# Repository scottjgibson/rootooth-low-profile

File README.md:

rootooth-low-profile
====================

My implementation of a bluetooth roomba interface.  It's very low profile and low cost

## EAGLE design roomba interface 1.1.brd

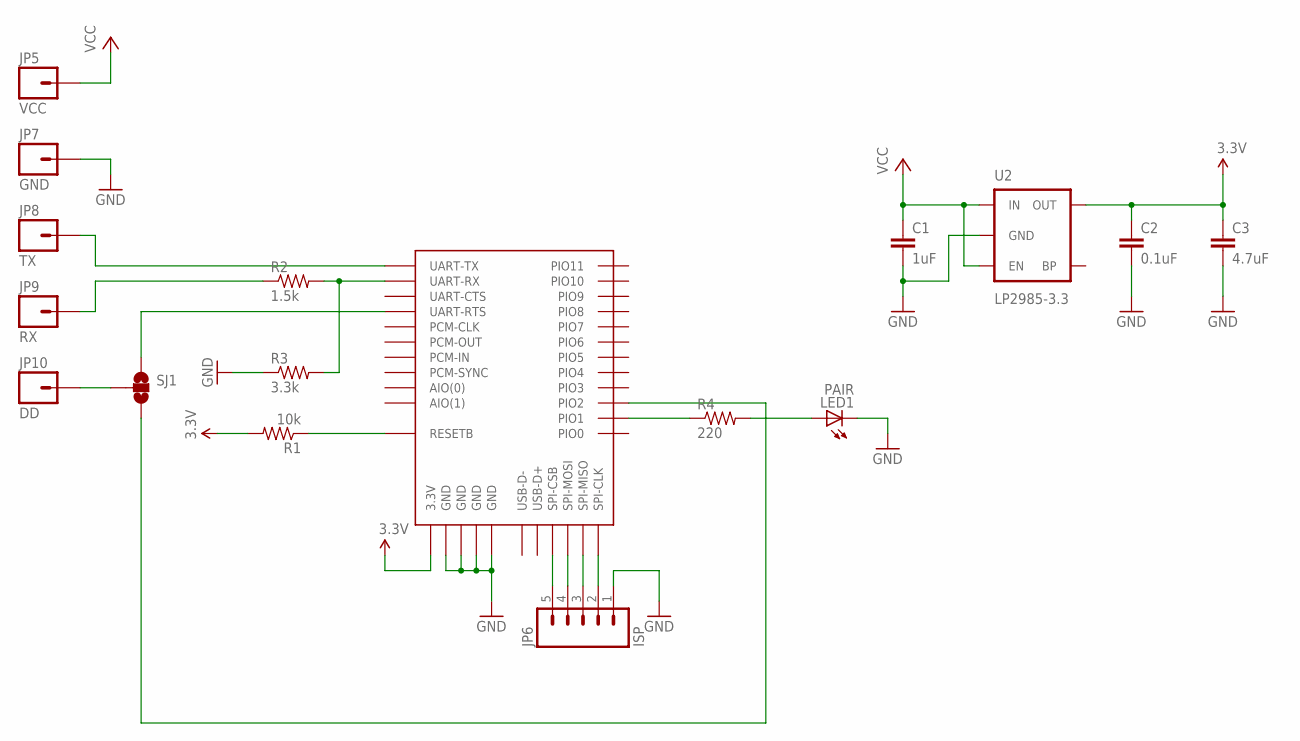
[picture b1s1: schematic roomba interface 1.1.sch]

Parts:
C1: 1uF; 0805
C2: 0.1uF; 0805
C3: 4.7uF; 0805
JP5: VCC; 1X01
JP6: ISP; 1X05
JP7: GND; 1X01
JP8: TX; 1X01
JP9: RX; 1X01
JP10: DD; 1X01
LED1: PAIR; LED-0603
R1: 10k; 0805
R2: 1.5k; 0805
R3: 3.3k; 0805
R4: 220; 0805
SJ1: SOLDERJUMPER_2WAYT; SJ_2
U2: LP2985-3.3; SOT23-5
U$1: BTM400_6B

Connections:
3.3V: C2.1, C3.1, R1.2, U2.5 (OUT), U$1.3.3V
GND: C1.2, C2.2, C3.2, JP6.1, JP7.1, LED1.C, R3.1, U2.2 (GND), U$1.GND@1 (GND), U$1.GND@2 (GND), U$1.GND@3 (GND), U$1.GND@4 (GND)
unnamed: R1.1, U$1.RESETB
unnamed: JP9.1, R2.1
unnamed: R2.2, R3.2, U$1.UART-RX
unnamed: JP8.1, U$1.UART-TX
unnamed: JP6.5, U$1.SPI-CSB
unnamed: JP6.4, U$1.SPI-MOSI
unnamed: JP6.3, U$1.SPI-MISO
unnamed: JP6.2, U$1.SPI-CLK
unnamed: SJ1.1, U$1.UART-RTS
unnamed: R4.1, U$1.PIO(1) (PIO1)
unnamed: LED1.A, R4.2
unnamed: JP10.1, SJ1.2
unnamed: SJ1.3, U$1.PIO(2) (PIO2)
VCC: C1.1, JP5.1, U2.1 (IN), U2.3 (EN)

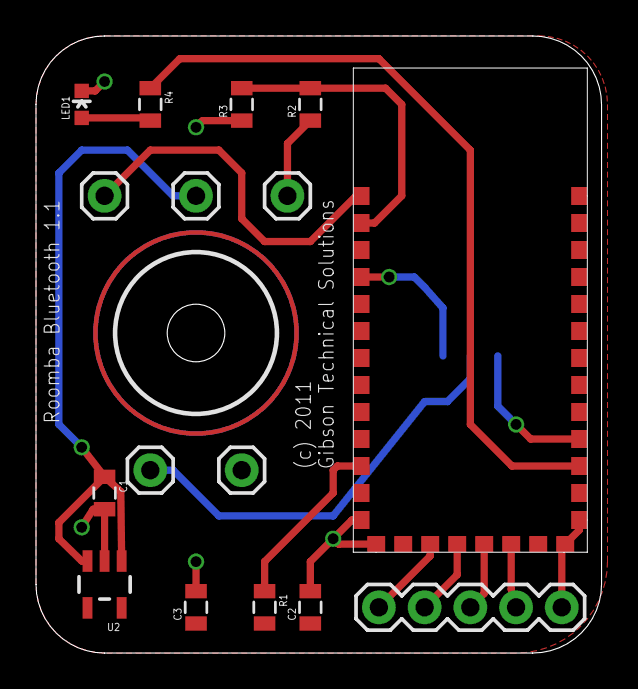
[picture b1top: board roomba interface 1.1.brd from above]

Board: 2 copper layers, 31.4 x 34.3 mm, 17 parts (1 on the bottom side), 16 nets.

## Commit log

2013-11-24 Version 1.1

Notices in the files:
roomba interface 1.1.brd:
(c) 2011
